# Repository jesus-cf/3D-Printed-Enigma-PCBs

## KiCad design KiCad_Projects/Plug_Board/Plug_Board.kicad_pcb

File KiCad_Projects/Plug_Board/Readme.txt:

This folder contains the KiCad files for the plug board.

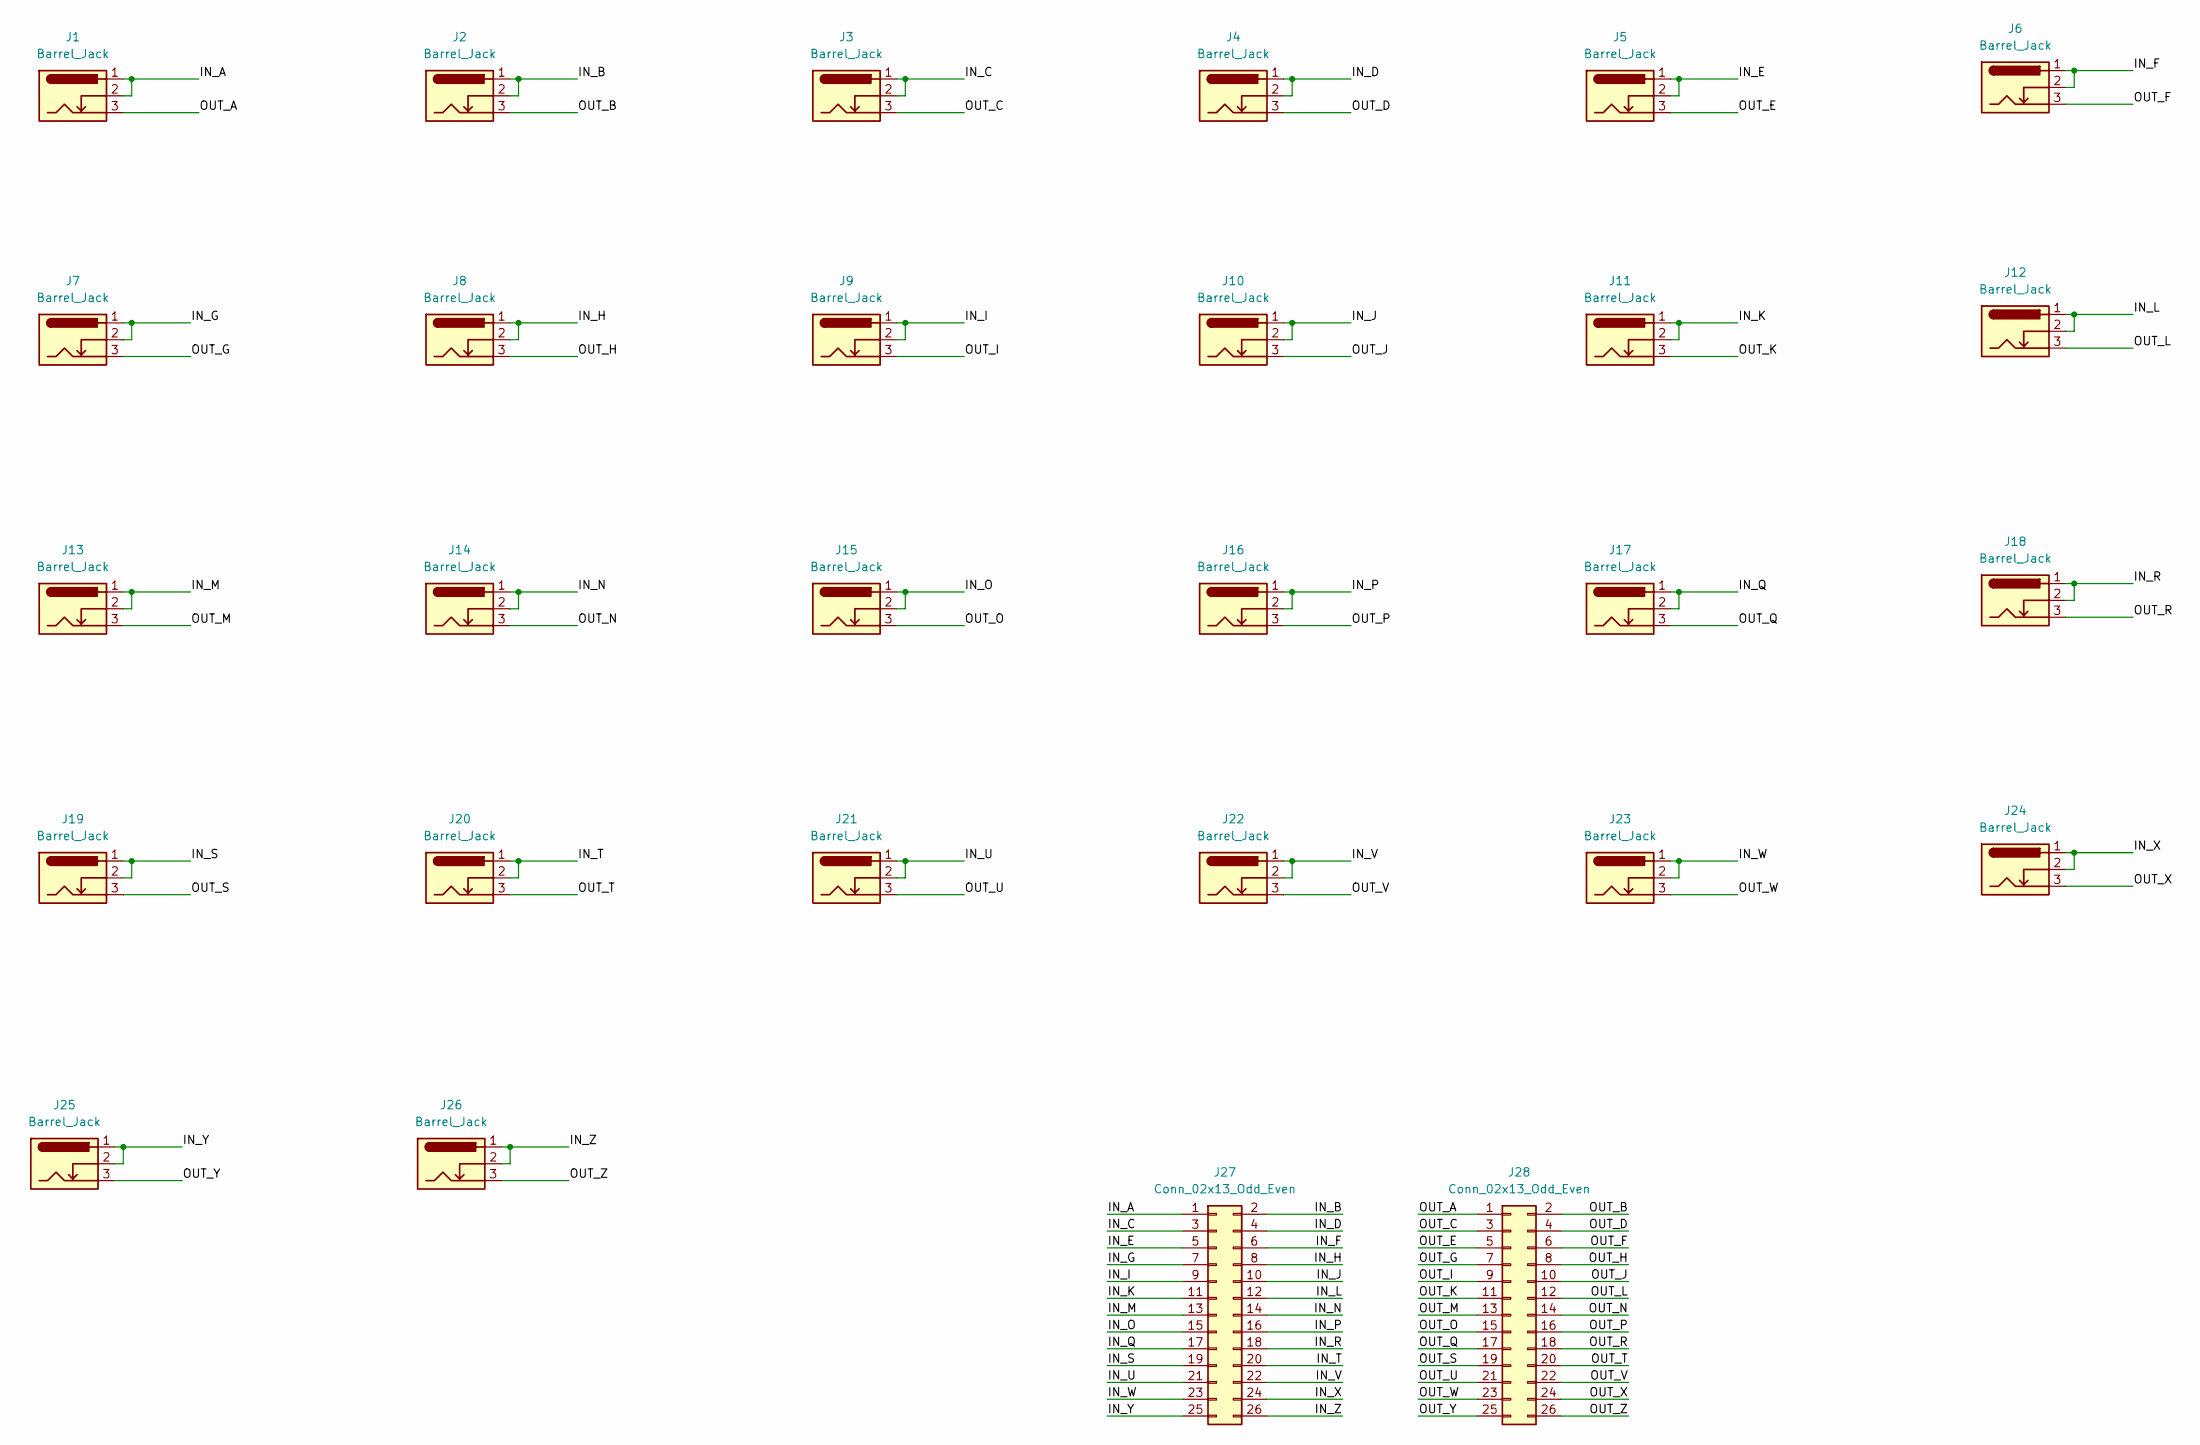
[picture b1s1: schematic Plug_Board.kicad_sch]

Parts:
J1, J2, J3, J4, J5, J6, J7, J8, J9, J10, J11, J12, J13, J14, J15, J16, J17, J18, J19, J20, J21, J22, J23, J24, J25, J26: Barrel_Jack; LDC-130T1-Oblong
J27, J28: Conn_02x13_Odd_Even; PinHeader_2x13_P2.54mm_Vertical_both_sides

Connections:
/IN_A: J1.1, J1.2, J27.1
/IN_B: J2.1, J2.2, J27.2
/IN_C: J3.1, J3.2, J27.3
/IN_D: J4.1, J4.2, J27.4
/IN_E: J5.1, J5.2, J27.5
/IN_F: J6.1, J6.2, J27.6
/IN_G: J7.1, J7.2, J27.7
/IN_H: J8.1, J8.2, J27.8
/IN_I: J9.1, J9.2, J27.9
/IN_J: J10.1, J10.2, J27.10
/IN_K: J11.1, J11.2, J27.11
/IN_L: J12.1, J12.2, J27.12
/IN_M: J13.1, J13.2, J27.13
/IN_N: J14.1, J14.2, J27.14
/IN_O: J15.1, J15.2, J27.15
/IN_P: J16.1, J16.2, J27.16
/IN_Q: J17.1, J17.2, J27.17
/IN_R: J18.1, J18.2, J27.18
/IN_S: J19.1, J19.2, J27.19
/IN_T: J20.1, J20.2, J27.20
/IN_U: J21.1, J21.2, J27.21
/IN_V: J22.1, J22.2, J27.22
/IN_W: J23.1, J23.2, J27.23
/IN_X: J24.1, J24.2, J27.24
/IN_Y: J25.1, J25.2, J27.25
/IN_Z: J26.1, J26.2, J27.26
/OUT_A: J1.3, J28.1
/OUT_B: J2.3, J28.2
/OUT_C: J3.3, J28.3
/OUT_D: J4.3, J28.4
/OUT_E: J5.3, J28.5
/OUT_F: J6.3, J28.6
/OUT_G: J7.3, J28.7
/OUT_H: J8.3, J28.8
/OUT_I: J9.3, J28.9
/OUT_J: J10.3, J28.10
/OUT_K: J11.3, J28.11
/OUT_L: J12.3, J28.12
/OUT_M: J13.3, J28.13
/OUT_N: J14.3, J28.14
/OUT_O: J15.3, J28.15
/OUT_P: J16.3, J28.16
/OUT_Q: J17.3, J28.17
/OUT_R: J18.3, J28.18
/OUT_S: J19.3, J28.19
/OUT_T: J20.3, J28.20
/OUT_U: J21.3, J28.21
/OUT_V: J22.3, J28.22
/OUT_W: J23.3, J28.23
/OUT_X: J24.3, J28.24
/OUT_Y: J25.3, J28.25
/OUT_Z: J26.3, J28.26

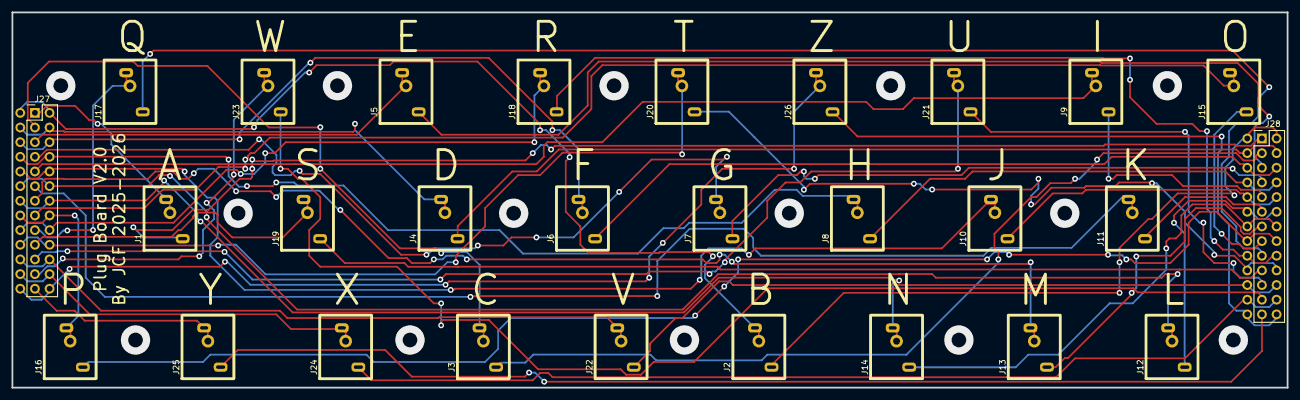
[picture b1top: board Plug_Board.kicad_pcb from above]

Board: 2 copper layers, 221.0 x 65.0 mm, 28 parts (0 on the bottom side), 52 nets.

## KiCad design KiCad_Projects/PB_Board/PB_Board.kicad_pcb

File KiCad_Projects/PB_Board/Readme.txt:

In this folder are the key board KiCad files.

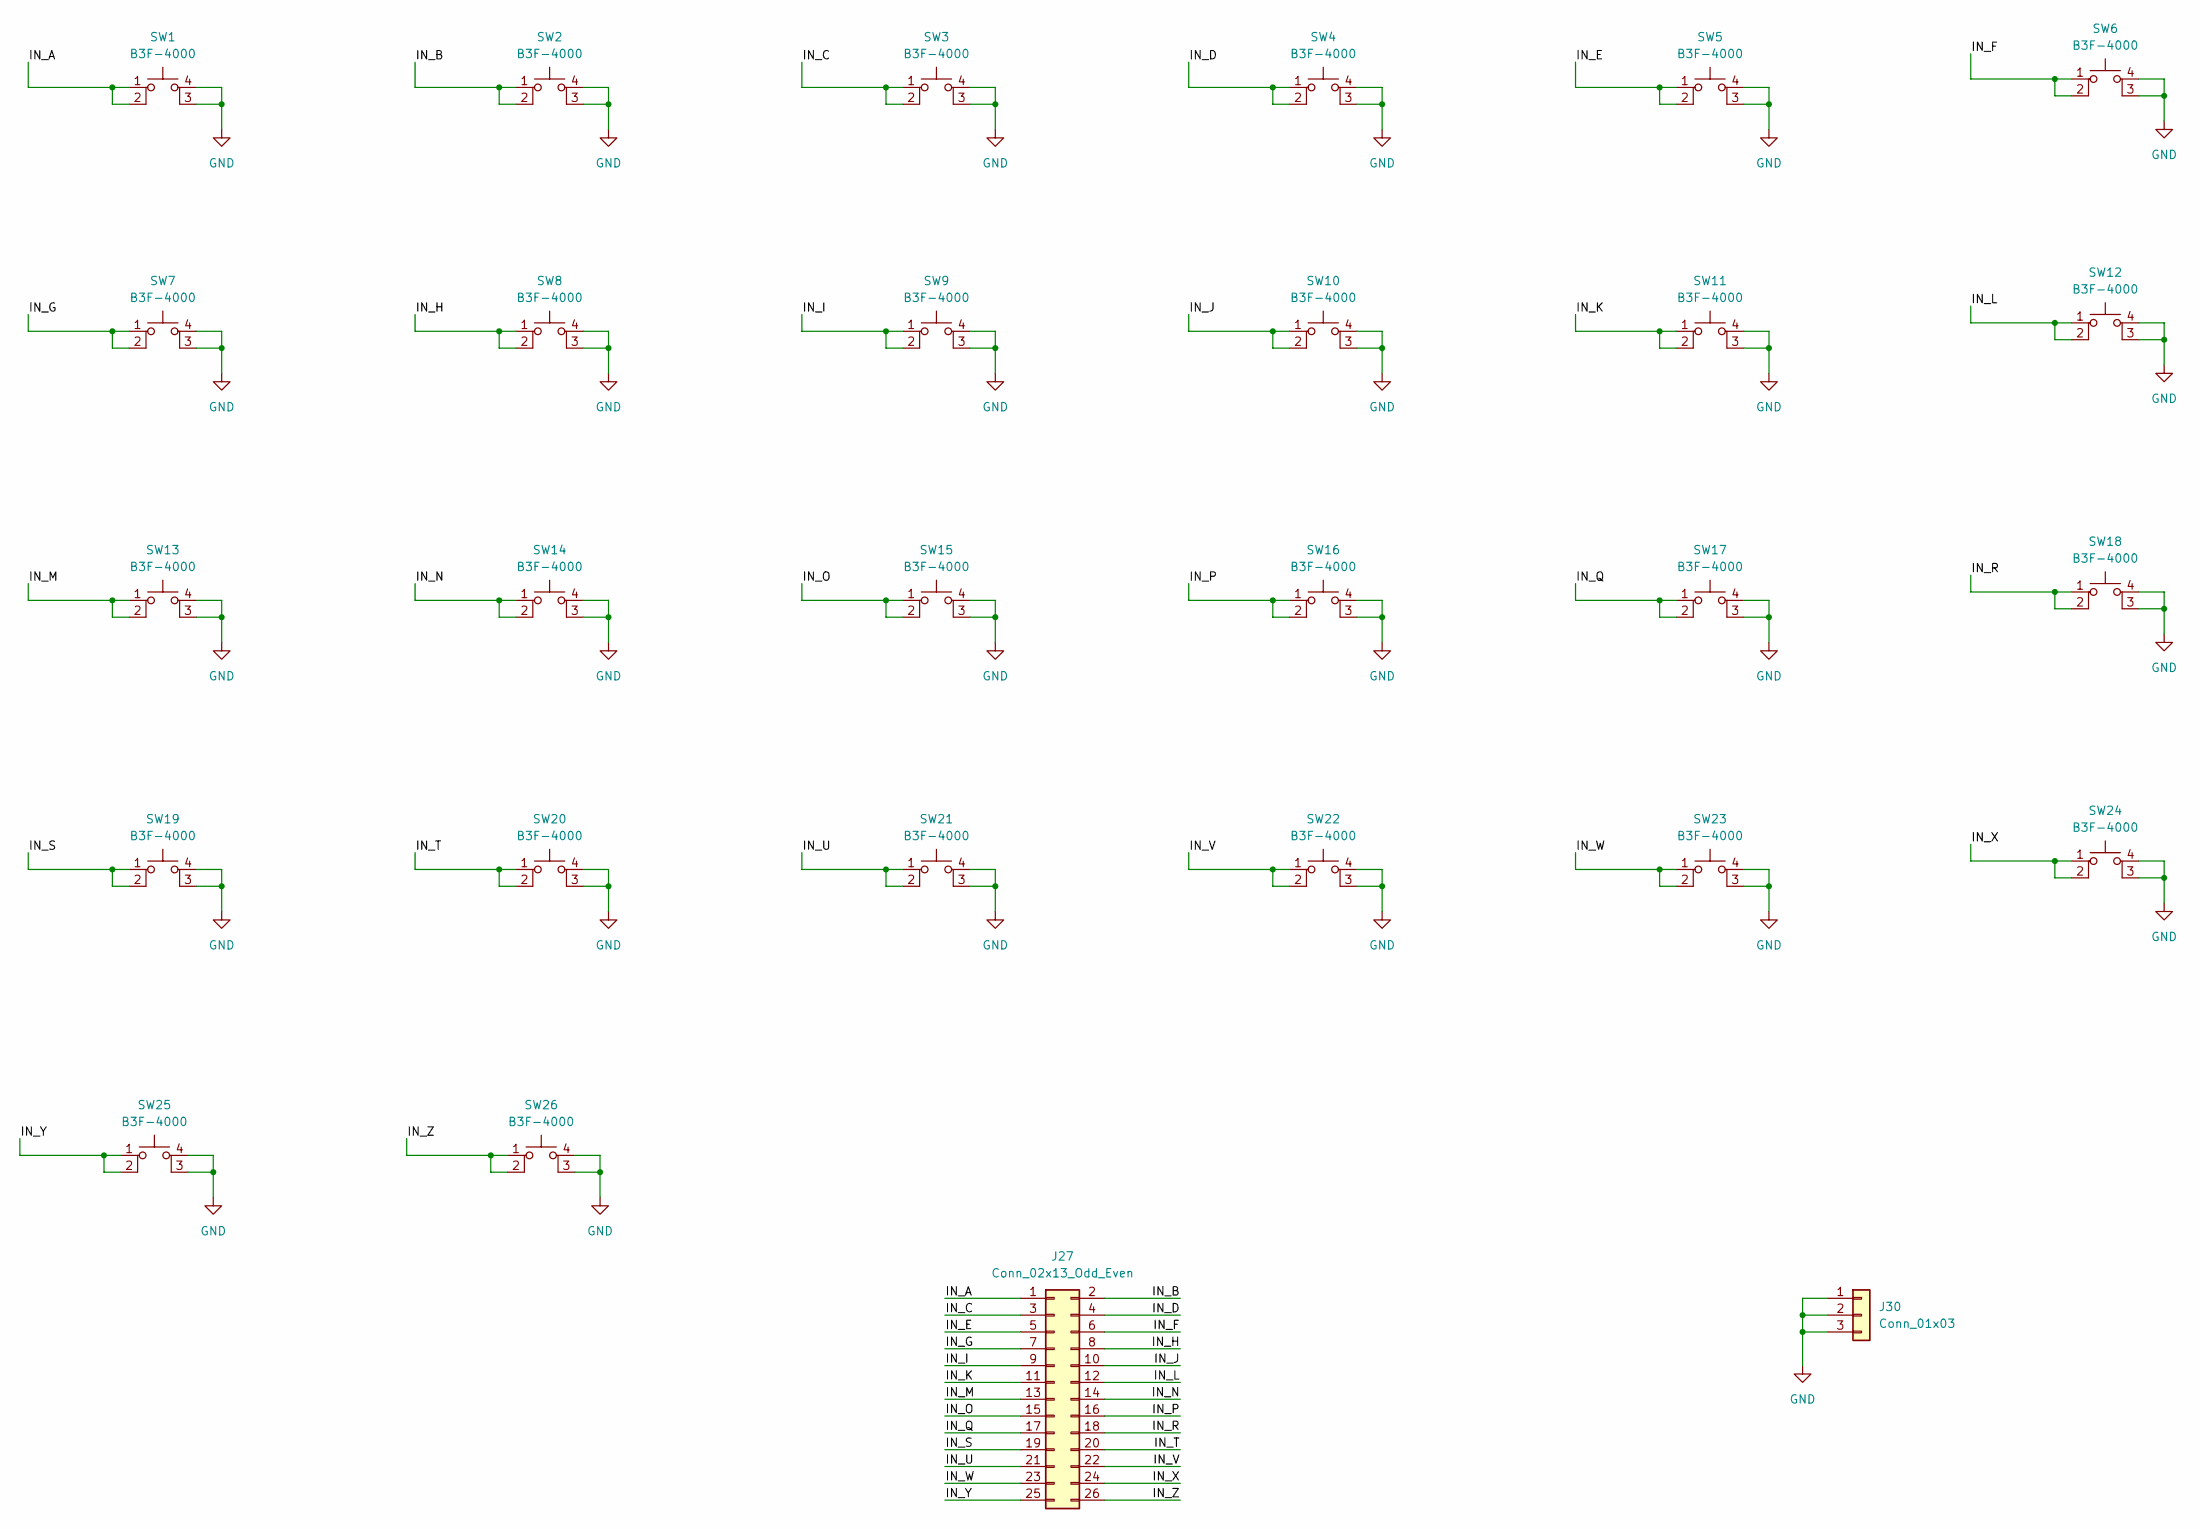
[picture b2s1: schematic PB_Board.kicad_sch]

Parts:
J27: Conn_02x13_Odd_Even; PinHeader_2x13_P2.54mm_Vertical_both_sides
J30: Conn_01x03; PinHeader_1x03_P2.54mm_Vertical
SW1, SW2, SW3, SW4, SW5, SW6, SW7, SW8, SW9, SW10, SW11, SW12, SW13, SW14, SW15, SW16, SW17, SW18, SW19, SW20, SW21, SW22, SW23, SW24, SW25, SW26: B3F-4000

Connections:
/IN_A: J27.1, SW1.1, SW1.2
/IN_B: J27.2, SW2.1, SW2.2
/IN_C: J27.3, SW3.1, SW3.2
/IN_D: J27.4, SW4.1, SW4.2
/IN_E: J27.5, SW5.1, SW5.2
/IN_F: J27.6, SW6.1, SW6.2
/IN_G: J27.7, SW7.1, SW7.2
/IN_H: J27.8, SW8.1, SW8.2
/IN_I: J27.9, SW9.1, SW9.2
/IN_J: J27.10, SW10.1, SW10.2
/IN_K: J27.11, SW11.1, SW11.2
/IN_L: J27.12, SW12.1, SW12.2
/IN_M: J27.13, SW13.1, SW13.2
/IN_N: J27.14, SW14.1, SW14.2
/IN_O: J27.15, SW15.1, SW15.2
/IN_P: J27.16, SW16.1, SW16.2
/IN_Q: J27.17, SW17.1, SW17.2
/IN_R: J27.18, SW18.1, SW18.2
/IN_S: J27.19, SW19.1, SW19.2
/IN_T: J27.20, SW20.1, SW20.2
/IN_U: J27.21, SW21.1, SW21.2
/IN_V: J27.22, SW22.1, SW22.2
/IN_W: J27.23, SW23.1, SW23.2
/IN_X: J27.24, SW24.1, SW24.2
/IN_Y: J27.25, SW25.1, SW25.2
/IN_Z: J27.26, SW26.1, SW26.2
GND: J30.1, J30.2, J30.3, SW1.3 (K), SW1.4 (A), SW2.3 (K), SW2.4 (A), SW3.3 (K), SW3.4 (A), SW4.3 (K), SW4.4 (A), SW5.3 (K), SW5.4 (A), SW6.3 (K), SW6.4 (A), SW7.3 (K), SW7.4 (A), SW8.3 (K), SW8.4 (A), SW9.3 (K), SW9.4 (A), SW10.3 (K), SW10.4 (A), SW11.3 (K), SW11.4 (A), SW12.3 (K), SW12.4 (A), SW13.3 (K), SW13.4 (A), SW14.3 (K), SW14.4 (A), SW15.3 (K), SW15.4 (A), SW16.3 (K), SW16.4 (A), SW17.3 (K), SW17.4 (A), SW18.3 (K), SW18.4 (A), SW19.3 (K), SW19.4 (A), SW20.3 (K), SW20.4 (A), SW21.3 (K), SW21.4 (A), SW22.3 (K), SW22.4 (A), SW23.3 (K), SW23.4 (A), SW24.3 (K), SW24.4 (A), SW25.3 (K), SW25.4 (A), SW26.3 (K), SW26.4 (A)

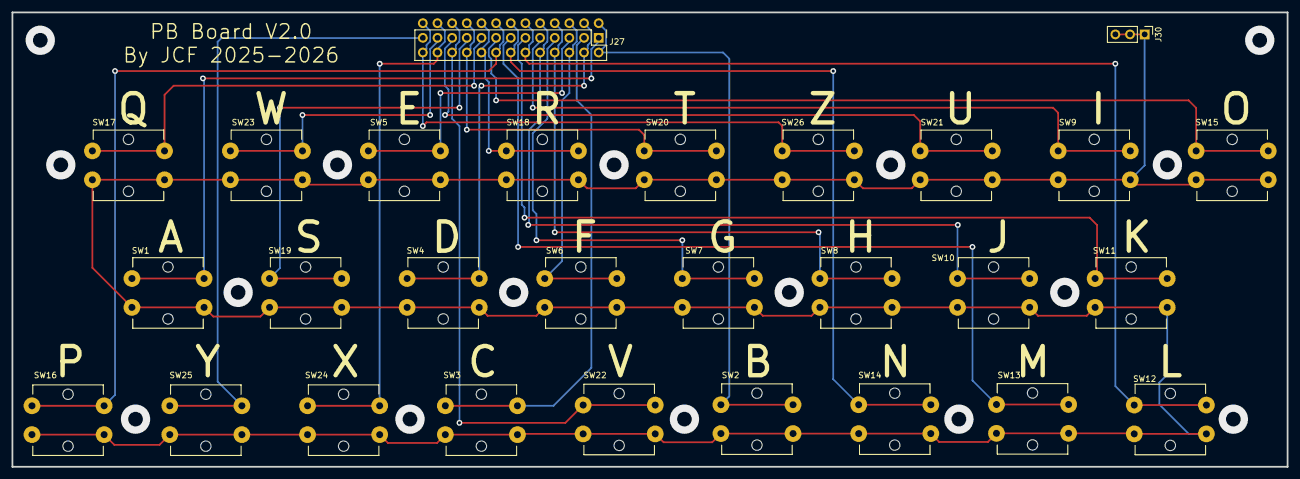
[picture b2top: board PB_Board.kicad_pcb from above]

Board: 2 copper layers, 221.0 x 78.7 mm, 28 parts (0 on the bottom side), 27 nets.

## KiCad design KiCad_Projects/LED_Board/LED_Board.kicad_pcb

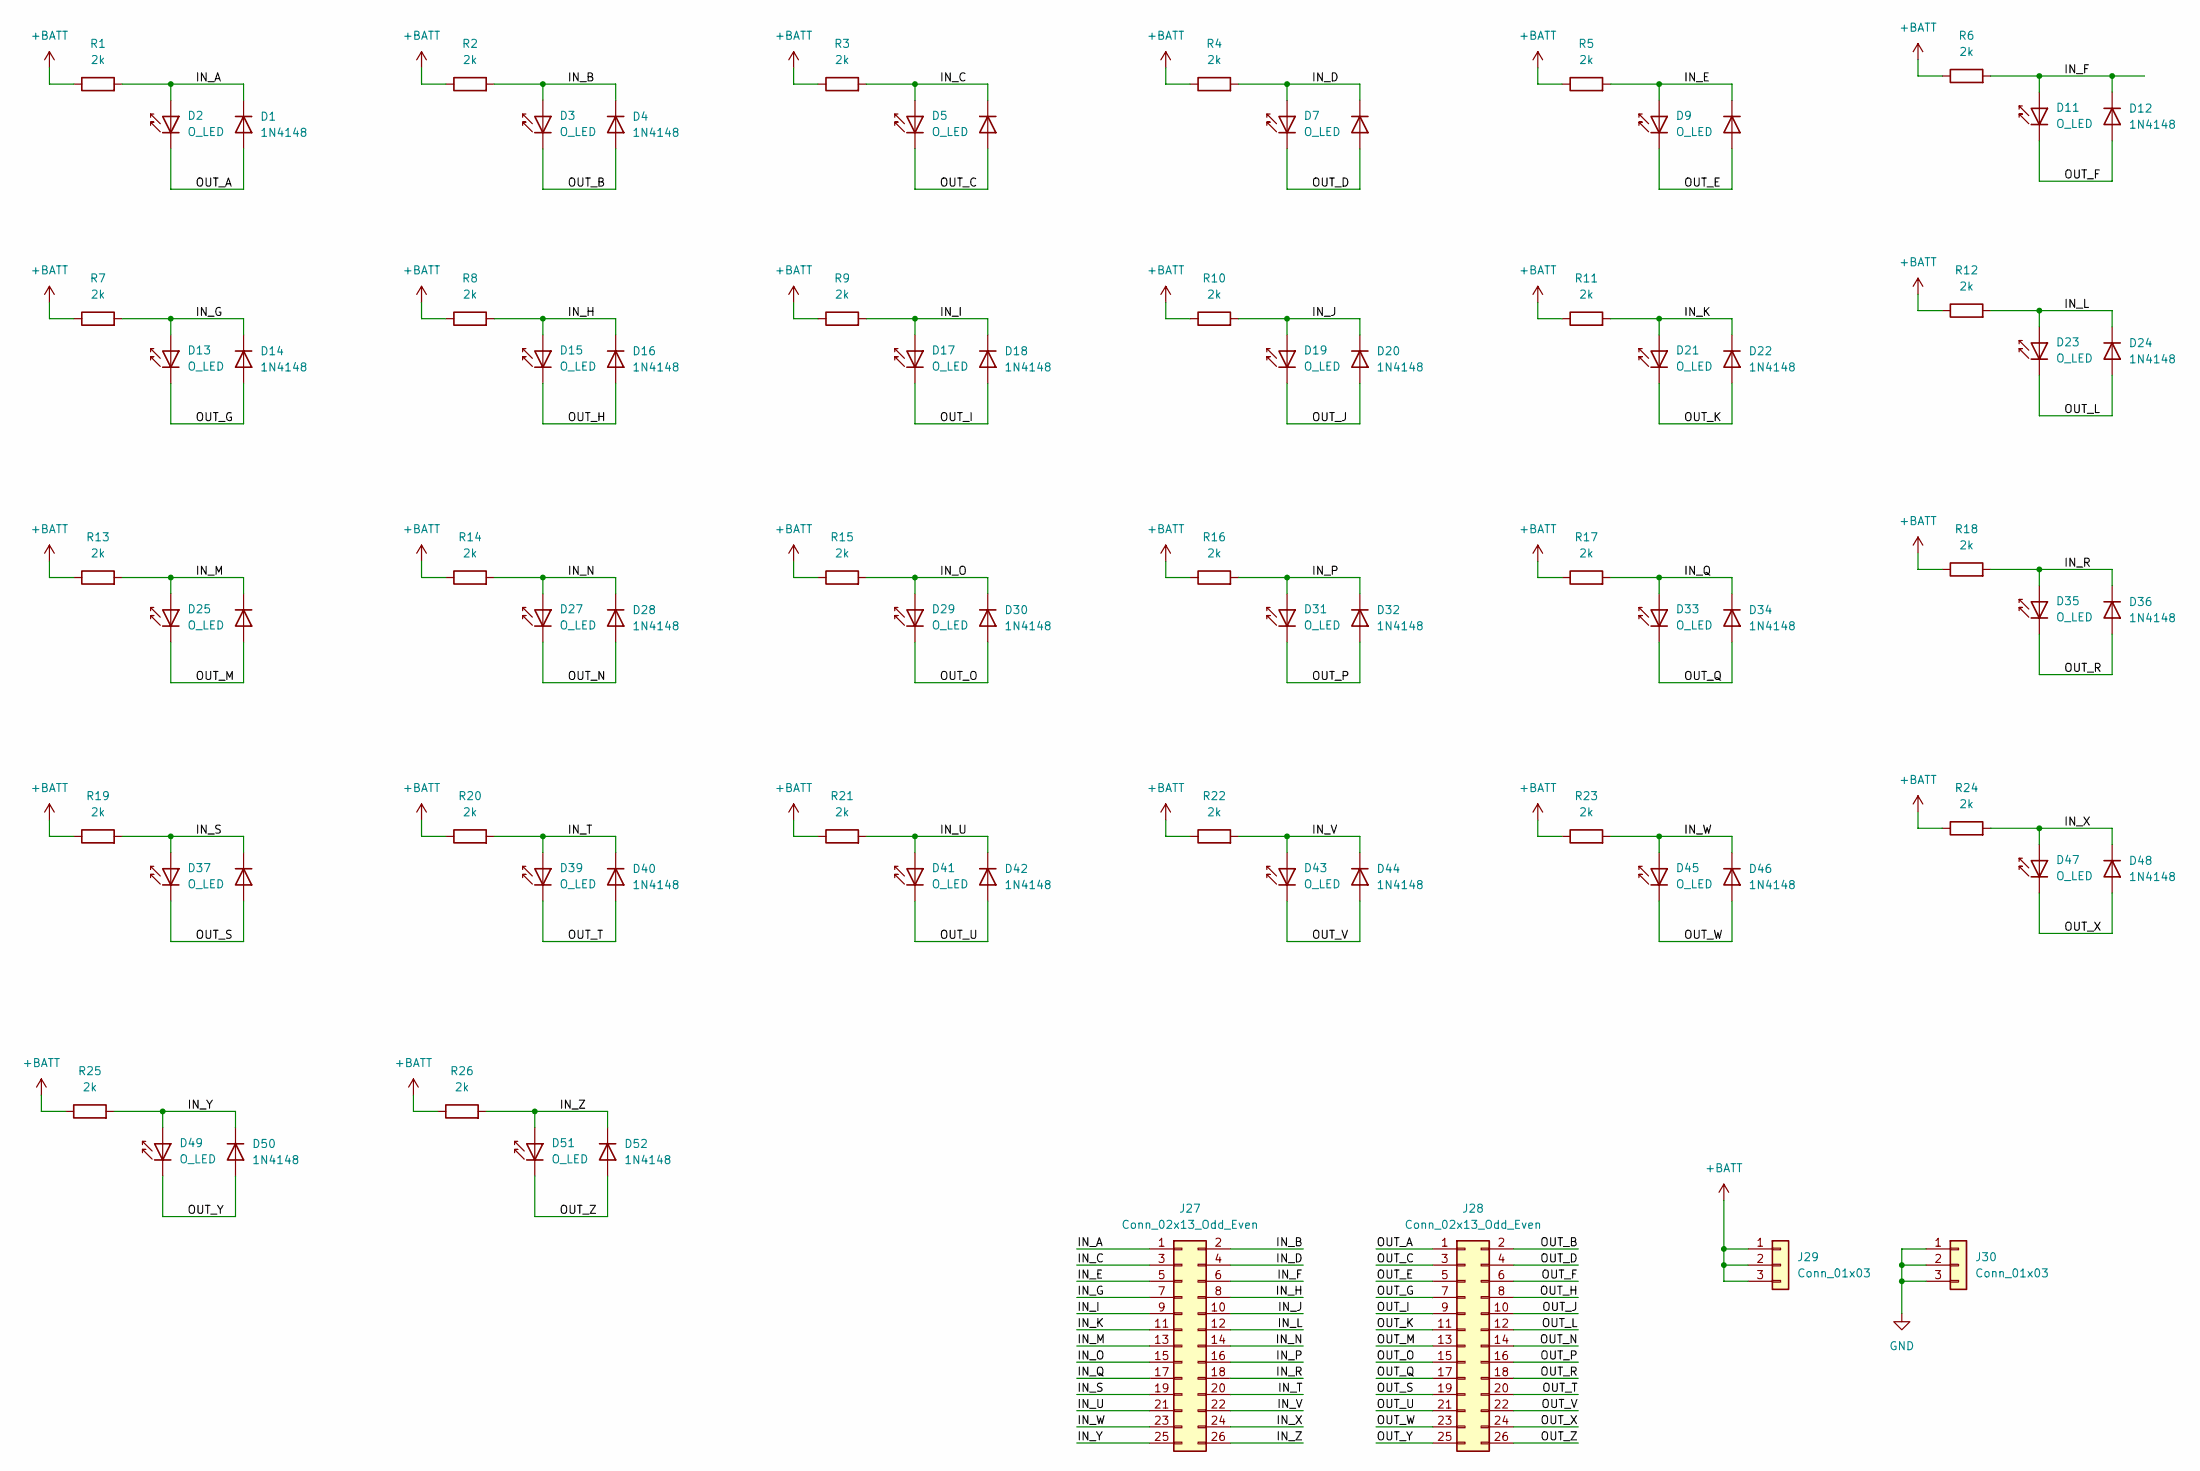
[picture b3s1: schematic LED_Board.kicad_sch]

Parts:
D1, D4, D6, D8, D10, D12, D14, D16, D18, D20, D22, D24, D26, D28, D30, D32, D34, D36, D38, D40, D42, D44, D46, D48, D50, D52: 1N4148; D_DO-35_SOD27_P7.62mm_Horizontal
D2, D3, D5, D7, D9, D11, D13, D15, D17, D19, D21, D23, D25, D27, D29, D31, D33, D35, D37, D39, D41, D43, D45, D47, D49, D51: O_LED; LED_D5.0mm_IRGrey
J27, J28: Conn_02x13_Odd_Even; PinHeader_2x13_P2.54mm_Vertical_both_sides
J29, J30: Conn_01x03; PinHeader_1x03_P2.54mm_Vertical
R1, R2, R3, R4, R5, R6, R7, R8, R9, R10, R11, R12, R13, R14, R15, R16, R17, R18, R19, R20, R21, R22, R23, R24, R25, R26: 2k; R_Axial_DIN0207_L6.3mm_D2.5mm_P10.16mm_Horizontal

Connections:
+BATT: J29.1, J29.2, J29.3, R1.1, R2.1, R3.1, R4.1, R5.1, R6.1, R7.1, R8.1, R9.1, R10.1, R11.1, R12.1, R13.1, R14.1, R15.1, R16.1, R17.1, R18.1, R19.1, R20.1, R21.1, R22.1, R23.1, R24.1, R25.1, R26.1
/IN_A: D1.1 (K), D2.2 (A), J27.1, R1.2
/IN_B: D3.2 (A), D4.1 (K), J27.2, R2.2
/IN_C: D5.2 (A), D6.1 (K), J27.3, R3.2
/IN_D: D7.2 (A), D8.1 (K), J27.4, R4.2
/IN_E: D9.2 (A), D10.1 (K), J27.5, R5.2
/IN_F: D11.2 (A), D12.1 (K), J27.6, R6.2
/IN_G: D13.2 (A), D14.1 (K), J27.7, R7.2
/IN_H: D15.2 (A), D16.1 (K), J27.8, R8.2
/IN_I: D17.2 (A), D18.1 (K), J27.9, R9.2
/IN_J: D19.2 (A), D20.1 (K), J27.10, R10.2
/IN_K: D21.2 (A), D22.1 (K), J27.11, R11.2
/IN_L: D23.2 (A), D24.1 (K), J27.12, R12.2
/IN_M: D25.2 (A), D26.1 (K), J27.13, R13.2
/IN_N: D27.2 (A), D28.1 (K), J27.14, R14.2
/IN_O: D29.2 (A), D30.1 (K), J27.15, R15.2
/IN_P: D31.2 (A), D32.1 (K), J27.16, R16.2
/IN_Q: D33.2 (A), D34.1 (K), J27.17, R17.2
/IN_R: D35.2 (A), D36.1 (K), J27.18, R18.2
/IN_S: D37.2 (A), D38.1 (K), J27.19, R19.2
/IN_T: D39.2 (A), D40.1 (K), J27.20, R20.2
/IN_U: D41.2 (A), D42.1 (K), J27.21, R21.2
/IN_V: D43.2 (A), D44.1 (K), J27.22, R22.2
/IN_W: D45.2 (A), D46.1 (K), J27.23, R23.2
/IN_X: D47.2 (A), D48.1 (K), J27.24, R24.2
/IN_Y: D49.2 (A), D50.1 (K), J27.25, R25.2
/IN_Z: D51.2 (A), D52.1 (K), J27.26, R26.2
/OUT_A: D1.2 (A), D2.1 (K), J28.1
/OUT_B: D3.1 (K), D4.2 (A), J28.2
/OUT_C: D5.1 (K), D6.2 (A), J28.3
/OUT_D: D7.1 (K), D8.2 (A), J28.4
/OUT_E: D9.1 (K), D10.2 (A), J28.5
/OUT_F: D11.1 (K), D12.2 (A), J28.6
/OUT_G: D13.1 (K), D14.2 (A), J28.7
/OUT_H: D15.1 (K), D16.2 (A), J28.8
/OUT_I: D17.1 (K), D18.2 (A), J28.9
/OUT_J: D19.1 (K), D20.2 (A), J28.10
/OUT_K: D21.1 (K), D22.2 (A), J28.11
/OUT_L: D23.1 (K), D24.2 (A), J28.12
/OUT_M: D25.1 (K), D26.2 (A), J28.13
/OUT_N: D27.1 (K), D28.2 (A), J28.14
/OUT_O: D29.1 (K), D30.2 (A), J28.15
/OUT_P: D31.1 (K), D32.2 (A), J28.16
/OUT_Q: D33.1 (K), D34.2 (A), J28.17
/OUT_R: D35.1 (K), D36.2 (A), J28.18
/OUT_S: D37.1 (K), D38.2 (A), J28.19
/OUT_T: D39.1 (K), D40.2 (A), J28.20
/OUT_U: D41.1 (K), D42.2 (A), J28.21
/OUT_V: D43.1 (K), D44.2 (A), J28.22
/OUT_W: D45.1 (K), D46.2 (A), J28.23
/OUT_X: D47.1 (K), D48.2 (A), J28.24
/OUT_Y: D49.1 (K), D50.2 (A), J28.25
/OUT_Z: D51.1 (K), D52.2 (A), J28.26
GND: J30.1, J30.2, J30.3

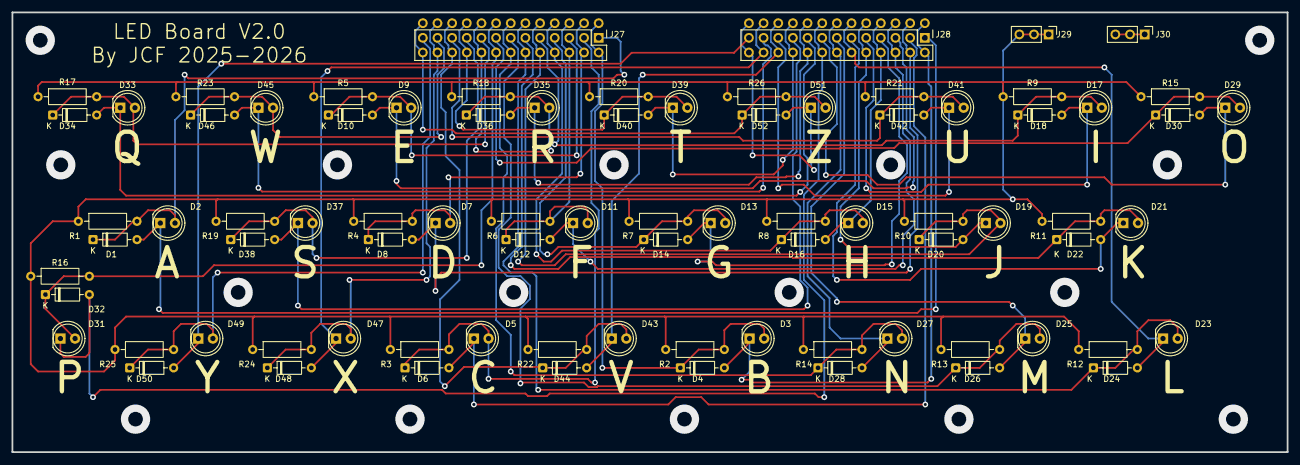
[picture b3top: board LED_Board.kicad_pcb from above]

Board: 2 copper layers, 221.0 x 76.2 mm, 82 parts (0 on the bottom side), 54 nets.
